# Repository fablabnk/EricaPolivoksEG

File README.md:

# Build Notes

- 2N3094 and 2N3096 have been abbreviated to 4 and 6 respectively on silkscreening
- only place NU 39K resistor if requiring -5V ... +5V output on INV EG OUT (presume otherwise get 0-10V)
- TP labels on schematic could actually be test points on the original PCB - check!

# TODO

TODO: check which DPDT footprint and remove "not verified" from layout - waiting on component
DONE: fully double check schematic against original
DONE: check IDC power pins & keying - stripe should be to -12V rail
DONE: check inverting (-) and non-inverting inputs (+) on TL074 in schematic by comparing to pinout
DONE: redo BOM - check we have 2.7k resistor! No, just 2.9K
DONE: are jacks switched/normalled? Yes pin 3 is engaged instead of pin 2 when the jack in unplugged
DONE: do not mix NPN (2N3904) and PNP (2N3906)
DONE: check diameter of radial caps
DONE: removed TP labels from schematic, can only presume they are useless!
DONE: removed pro power features: polyfuses, reverse polarity protection and inductors
DONE: LED orientation check
DONE: replaced R38 with 2,7k resistor. When 2.2 used and EG OUT is connected to certain VCAs, the looping may stop

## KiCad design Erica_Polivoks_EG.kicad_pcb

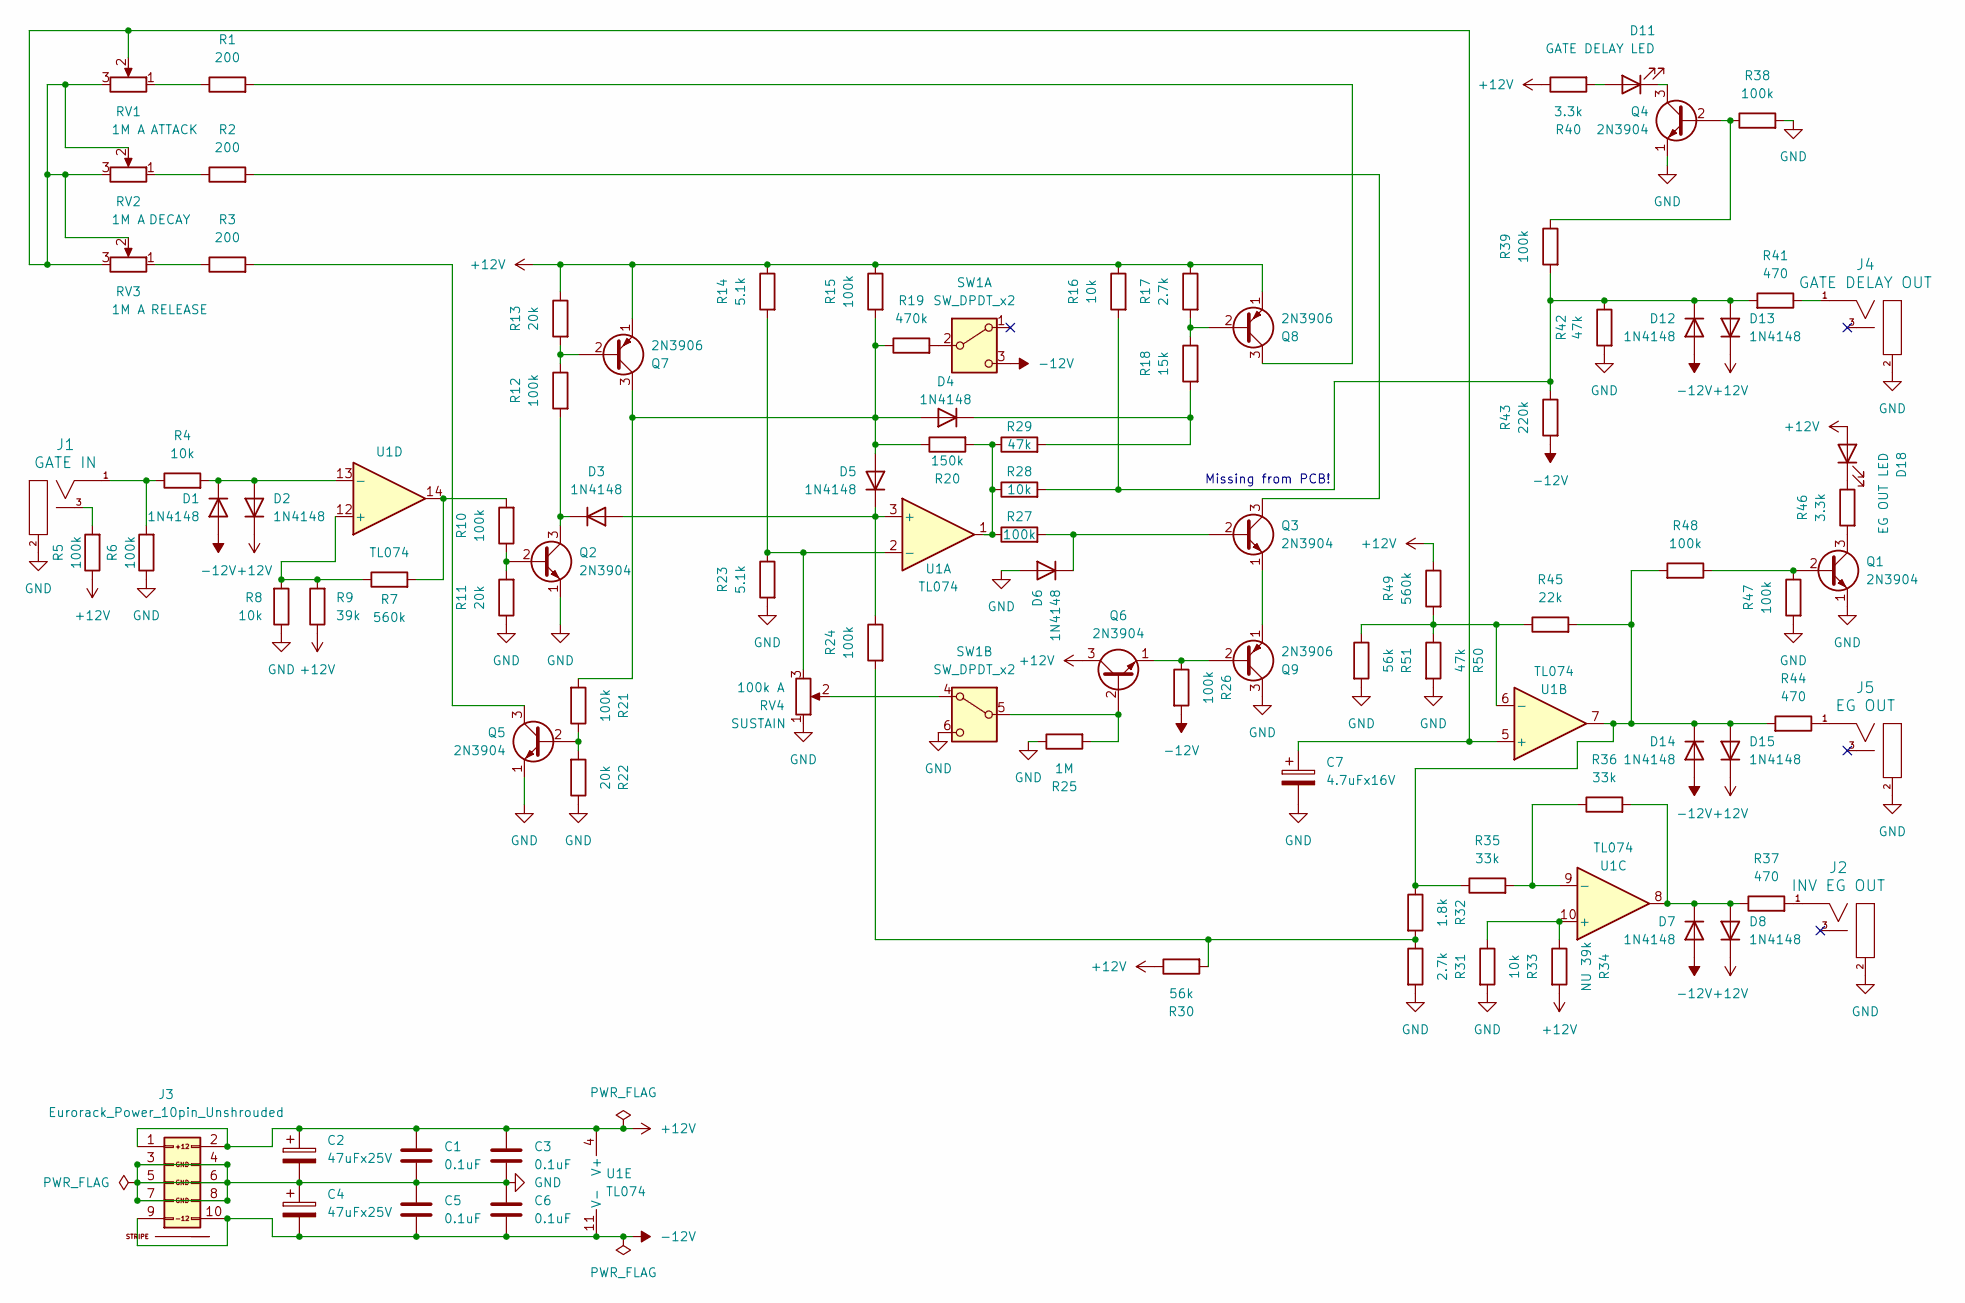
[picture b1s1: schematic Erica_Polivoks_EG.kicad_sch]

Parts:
C1, C3, C5, C6: 0.1uF; C_Disc_D3.0mm_W1.6mm_P2.50mm
C2, C4: 47uFx25V; CP_Radial_D5.0mm_P2.50mm
C7: 4.7uFx16V; CP_Radial_D5.0mm_P2.50mm
D1, D2, D3, D4, D5, D6, D7, D8, D12, D13, D14, D15: 1N4148; D_DO-35_SOD27_P7.62mm_Horizontal_Widened_No_K
D11, D18: LED; LED_3mm_C1A2
J1: GATE IN; EighthInch_PJ398SM_3mmNPTH; Part Number WQP-WQP518MA
J2: INV EG OUT; EighthInch_PJ398SM_3mmNPTH; Part Number WQP-WQP518MA
J3: Eurorack_Power_10pin_Unshrouded; IDC-Header_2x05_P2.54mm_Vertical_Euro_Power_Striped_Thicker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; Part Number 1-1002FBV0T
J4: GATE DELAY OUT; EighthInch_PJ398SM_3mmNPTH; Part Number WQP-WQP518MA
J5: EG OUT; EighthInch_PJ398SM_3mmNPTH; Part Number WQP-WQP518MA
Q1, Q2, Q3, Q4, Q5, Q6: 2N3904; TO-92L_Inline_Wider
Q7, Q8, Q9: 2N3906; TO-92L_Inline_Wider
R1, R2, R3: 200; R_Axial_DIN0204_L3.6mm_D1.6mm_P7.62mm_Horizontal_Widened
R4, R8, R16, R28, R33: 10k; R_Axial_DIN0204_L3.6mm_D1.6mm_P7.62mm_Horizontal_Widened
R5, R6, R10, R12, R15, R21, R24, R26, R27, R38, R39, R47, R48: 100k; R_Axial_DIN0204_L3.6mm_D1.6mm_P7.62mm_Horizontal_Widened
R7, R49: 560k; R_Axial_DIN0204_L3.6mm_D1.6mm_P7.62mm_Horizontal_Widened
R9: 39k; R_Axial_DIN0204_L3.6mm_D1.6mm_P7.62mm_Horizontal_Widened
R11, R13, R22: 20k; R_Axial_DIN0204_L3.6mm_D1.6mm_P7.62mm_Horizontal_Widened
R14, R23: 5.1k; R_Axial_DIN0204_L3.6mm_D1.6mm_P7.62mm_Horizontal_Widened
R17, R31: 2.7k; R_Axial_DIN0204_L3.6mm_D1.6mm_P7.62mm_Horizontal_Widened
R18: 15k; R_Axial_DIN0204_L3.6mm_D1.6mm_P7.62mm_Horizontal_Widened
R19: 470k; R_Axial_DIN0204_L3.6mm_D1.6mm_P7.62mm_Horizontal_Widened
R20: 150k; R_Axial_DIN0204_L3.6mm_D1.6mm_P7.62mm_Horizontal_Widened
R25: 1M; R_Axial_DIN0204_L3.6mm_D1.6mm_P7.62mm_Horizontal_Widened
R29, R42, R50: 47k; R_Axial_DIN0204_L3.6mm_D1.6mm_P7.62mm_Horizontal_Widened
R30, R51: 56k; R_Axial_DIN0204_L3.6mm_D1.6mm_P7.62mm_Horizontal_Widened
R32: 1.8k; R_Axial_DIN0204_L3.6mm_D1.6mm_P7.62mm_Horizontal_Widened
R34: NU 39k; R_Axial_DIN0204_L3.6mm_D1.6mm_P7.62mm_Horizontal_Widened
R35, R36: 33k; R_Axial_DIN0204_L3.6mm_D1.6mm_P7.62mm_Horizontal_Widened
R37, R41, R44: 470; R_Axial_DIN0204_L3.6mm_D1.6mm_P7.62mm_Horizontal_Widened
R40, R46: 3.3k; R_Axial_DIN0204_L3.6mm_D1.6mm_P7.62mm_Horizontal_Widened
R43: 220k; R_Axial_DIN0204_L3.6mm_D1.6mm_P7.62mm_Horizontal_Widened
R45: 22k; R_Axial_DIN0204_L3.6mm_D1.6mm_P7.62mm_Horizontal_Widened
RV1, RV2, RV3: 1M A; Pot_9mm_DShaft_RemovedPins4_5
RV4: 100k A; Pot_9mm_DShaft_RemovedPins4_5
SW1: SW_DPDT_x2; Switch_Toggle_DPDT_MS202
U1: TL074; DIP-14_W7.62mm_Socket

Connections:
+12V: C1.1, C2.1, C3.1, D2.1 (K), D8.1 (K), D13.1 (K), D15.1 (K), D18.2 (A), J3.1 (+12V), J3.2 (+12V), Q6.3 (C), Q7.1 (E), Q8.1 (E), R5.1, R9.1, R13.1, R14.1, R15.1, R16.1, R17.1, R30.1, R34.2, R40.1, R49.1, U1.4 (V+)
-12V: C4.2, C5.2, C6.2, D1.2 (A), D7.2 (A), D12.2 (A), D14.2 (A), J3.9 (-12V), J3.10 (-12V), R26.2, R43.2, SW1.3 (C), U1.11 (V-)
GND: C1.2, C2.2, C3.2, C4.1, C5.1, C6.1, C7.2, D6.2 (A), J1.2 (SHEILD), J2.2 (SHEILD), J3.3 (GND), J3.4 (GND), J3.5 (GND), J3.6 (GND), J3.7 (GND), J3.8 (GND), J4.2 (SHEILD), J5.2 (SHEILD), Q1.1 (E), Q2.1 (E), Q4.1 (E), Q5.1 (E), Q9.3 (C), R6.1, R8.1, R11.1, R22.1, R23.2, R25.1, R31.2, R33.2, R38.2, R42.2, R47.2, R50.2, R51.2, RV4.1, SW1.6 (C)
unnamed: D1.1 (K), D2.2 (A), R4.2, U1.13 (-)
unnamed: D3.2 (A), D5.1 (K), R24.1, U1.3 (+)
unnamed: D3.1 (K), Q2.3 (C), R12.2
unnamed: D4.2 (A), D5.2 (A), Q7.3 (C), R15.2, R19.1, R20.1, R21.2
unnamed: D4.1 (K), R18.2, R29.2
unnamed: D6.1 (K), Q3.2 (B), R27.2
unnamed: D7.1 (K), D8.2 (A), R36.2, R37.1, U1.8
unnamed: D11.2 (A), R40.2
unnamed: D11.1 (K), Q4.3 (C)
unnamed: D12.1 (K), D13.2 (A), R16.2, R28.2, R39.2, R41.2, R42.1, R43.1
unnamed: D14.1 (K), D15.2 (A), R32.1, R35.1, R44.2, R45.2, R48.2, U1.7
unnamed: D18.1 (K), R46.1
unnamed: J1.1 (SIG), R4.1, R6.2
unnamed: J1.3 (SW), R5.2
unnamed: J2.1 (SIG), R37.2
unnamed: J4.1 (SIG), R41.1
unnamed: J5.1 (SIG), R44.1
unnamed: Q1.2 (B), R47.1, R48.1
unnamed: Q1.3 (C), R46.2
unnamed: Q2.2 (B), R10.1, R11.2
unnamed: Q3.3 (C), R2.2
unnamed: Q3.1 (E), Q9.1 (E)
unnamed: Q4.2 (B), R38.1, R39.1
unnamed: Q5.2 (B), R21.1, R22.2
unnamed: Q5.3 (C), R3.2
unnamed: Q6.2 (B), R25.2, SW1.5 (B)
unnamed: Q6.1 (E), Q9.2 (B), R26.1
unnamed: Q7.2 (B), R12.1, R13.2
unnamed: Q8.2 (B), R17.2, R18.1
unnamed: Q8.3 (C), R1.2
unnamed: R1.1, RV1.1
unnamed: R2.1, RV2.1
unnamed: R3.1, RV3.1
unnamed: R7.2, R10.2, U1.14
unnamed: R20.2, R27.1, R28.1, R29.1, U1.1
unnamed: R24.2, R30.2, R31.1, R32.2
unnamed: R19.2, SW1.2 (B)
unnamed: RV4.2, SW1.4 (A)
unnamed: R14.2, R23.1, RV4.3, U1.2 (-)
unnamed: C7.1, RV1.2, RV1.3, RV2.2, RV2.3, RV3.2, RV3.3, U1.5 (+)
unnamed: R45.1, R49.2, R50.1, R51.1, U1.6 (-)
unnamed: R33.1, R34.1, U1.10 (+)
unnamed: R35.2, R36.1, U1.9 (-)
unnamed: R7.1, R8.2, R9.2, U1.12 (+)

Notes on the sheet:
Missing from PCB!

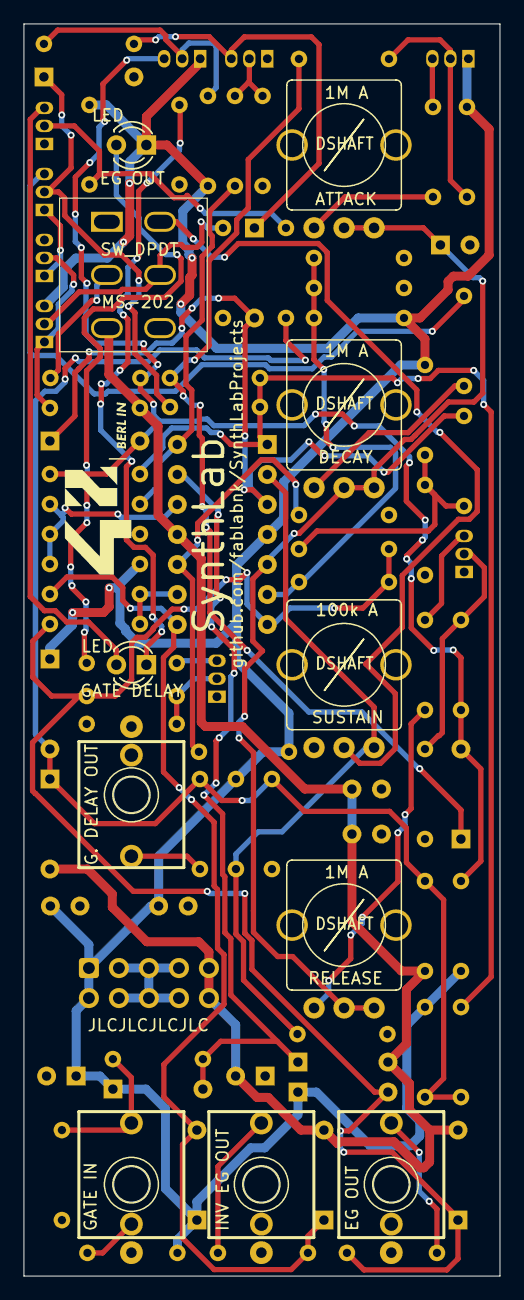
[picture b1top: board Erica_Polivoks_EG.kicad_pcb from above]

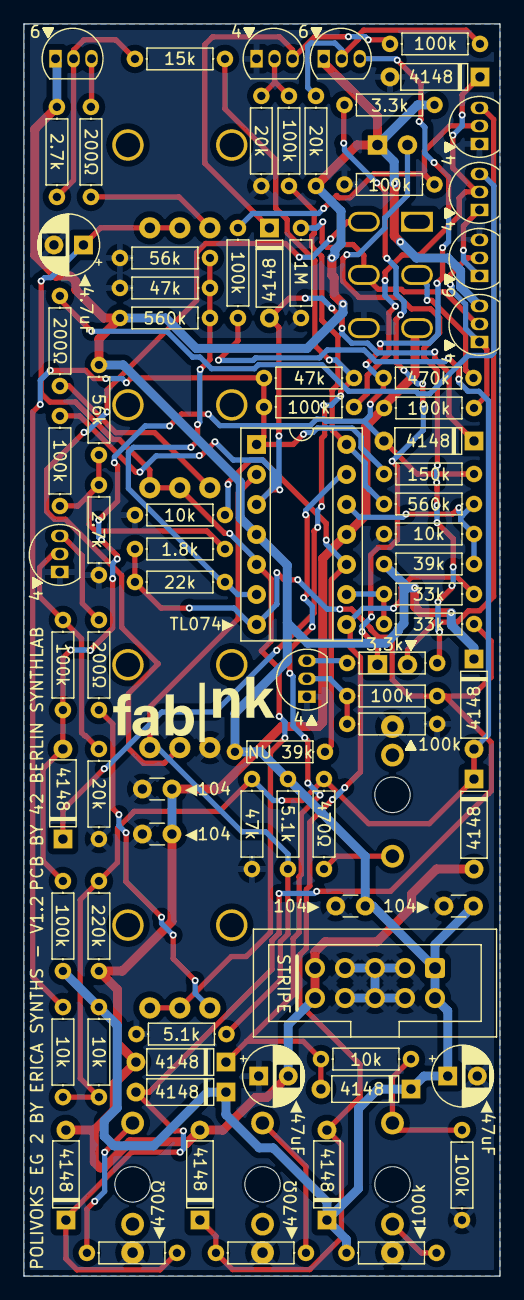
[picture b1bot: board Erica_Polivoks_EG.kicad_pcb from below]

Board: 2 copper layers, 40.3 x 106.0 mm, 92 parts (81 on the bottom side), 47 nets.

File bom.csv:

"Reference","Value","Datasheet","Footprint","Qty","DNP"
"C1,C3,C5,C6","0.1uF","~","","4",""
"C2,C4","47uFx25V","~","","2",""
"C7","4.7uFx16V","~","","1",""
"D1,D2,D3,D4,D5,D6,D7,D8,D12,D13,D14,D15","1N4148","https://assets.nexperia.com/documents/data-sheet/1N4148_1N4448.pdf","Diode_THT:D_DO-35_SOD27_P7.62mm_Horizontal","12",""
"D9,D10","1N4001","http://www.vishay.com/docs/88503/1n4001.pdf","Diode_THT:D_DO-41_SOD81_P10.16mm_Horizontal","2",""
"D11","GATE DELAY (YELLOW LED)","~","","1",""
"D18","EG OUT (YELLOW LED)","~","","1",""
"J1,J4,J5","GATE IN","","4ms_Jack:EighthInch_PJ398SM","3",""
"J2","INV EG OUT","","4ms_Jack:EighthInch_PJ398SM","1",""
"J3","Eurorack_Power_10pin_Unshrouded","","4ms_Connector:Pins_2x05_2.54mm_TH_Europower","1",""
"L1,L2","100uH","~","","2",""
"Q1,Q2,Q3,Q4,Q5,Q6","2N3904","https://www.onsemi.com/pub/Collateral/2N3903-D.PDF","Package_TO_SOT_THT:TO-92_Inline","6",""
"Q7,Q8,Q9","2N3906","https://www.onsemi.com/pub/Collateral/2N3906-D.PDF","Package_TO_SOT_THT:TO-92_Inline","3",""
"R1,R2,R3","200","~","","3",""
"R4,R8,R16,R28,R33","10k","~","","5",""
"R5,R6,R10,R12,R15,R21,R24,R26,R27,R38,R39,R47,R48","100k","~","","13",""
"R7,R49","560k","~","","2",""
"R9","39k","~","","1",""
"R11,R13,R22","20k","~","","3",""
"R14,R23","5.1k","~","","2",""
"R17","2.7k","~","","1",""
"R18","15k","~","","1",""
"R19","470k","~","","1",""
"R20","150k","~","","1",""
"R25","10M","~","","1",""
"R29,R42,R50","47k","~","","3",""
"R30,R51","56k","~","","2",""
"R31","2.2k","~","","1",""
"R32","1.8k","~","","1",""
"R34"," NU","~","","1",""
"R35,R36","33k","~","","2",""
"R37,R41,R44","470","~","","3",""
"R40,R46","3.3k","~","","2",""
"R43","220k","~","","1",""
"R45","22k","~","","1",""
"RV1","1M LOG ""ATTACK""","~","","1",""
"RV2","1M LOG ""DECAY""","~","","1",""
"RV3","1M LOG ""RELEASE""","~","","1",""
"RV4","100k LOG ""SUSTAIN""","~","","1",""
"SW1,SW2","SW_SPDT","~","","2",""
"U1","TL074","http://www.ti.com/lit/ds/symlink/tl071.pdf","","1",""

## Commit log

2024-07-27 initial duplication of the schematic
2024-07-27 passed ERC
2024-07-27 removed polyfuses, polarity protection diodes and inductors from power section of schematic
2024-07-27 schematic double checked
2024-07-29 pcb routed
2024-07-29 broke panel out into separate PCB file
2024-07-29 fixed silkscreening issues - just 'not verified' text issue remains
2024-07-29 almost ready to go
2024-08-10 waiting for DPDT switch to measure - otherwise complete
2024-08-13 v1.0 ready for production
2024-08-15 v1.0 ready for production - added actual HP-size outli]ne on User.Dawings layer
2024-09-15 added BuildNotes.md. Removed production folder
2024-09-15 Updated build notes
2024-09-16 most of V1.1 changes completed
2024-09-24 v1.1 ready for final check
2024-09-25 v1.1 checked
2024-12-01 updating after Dmitri's changes
2025-01-04 rerouting complete and passes DRC
